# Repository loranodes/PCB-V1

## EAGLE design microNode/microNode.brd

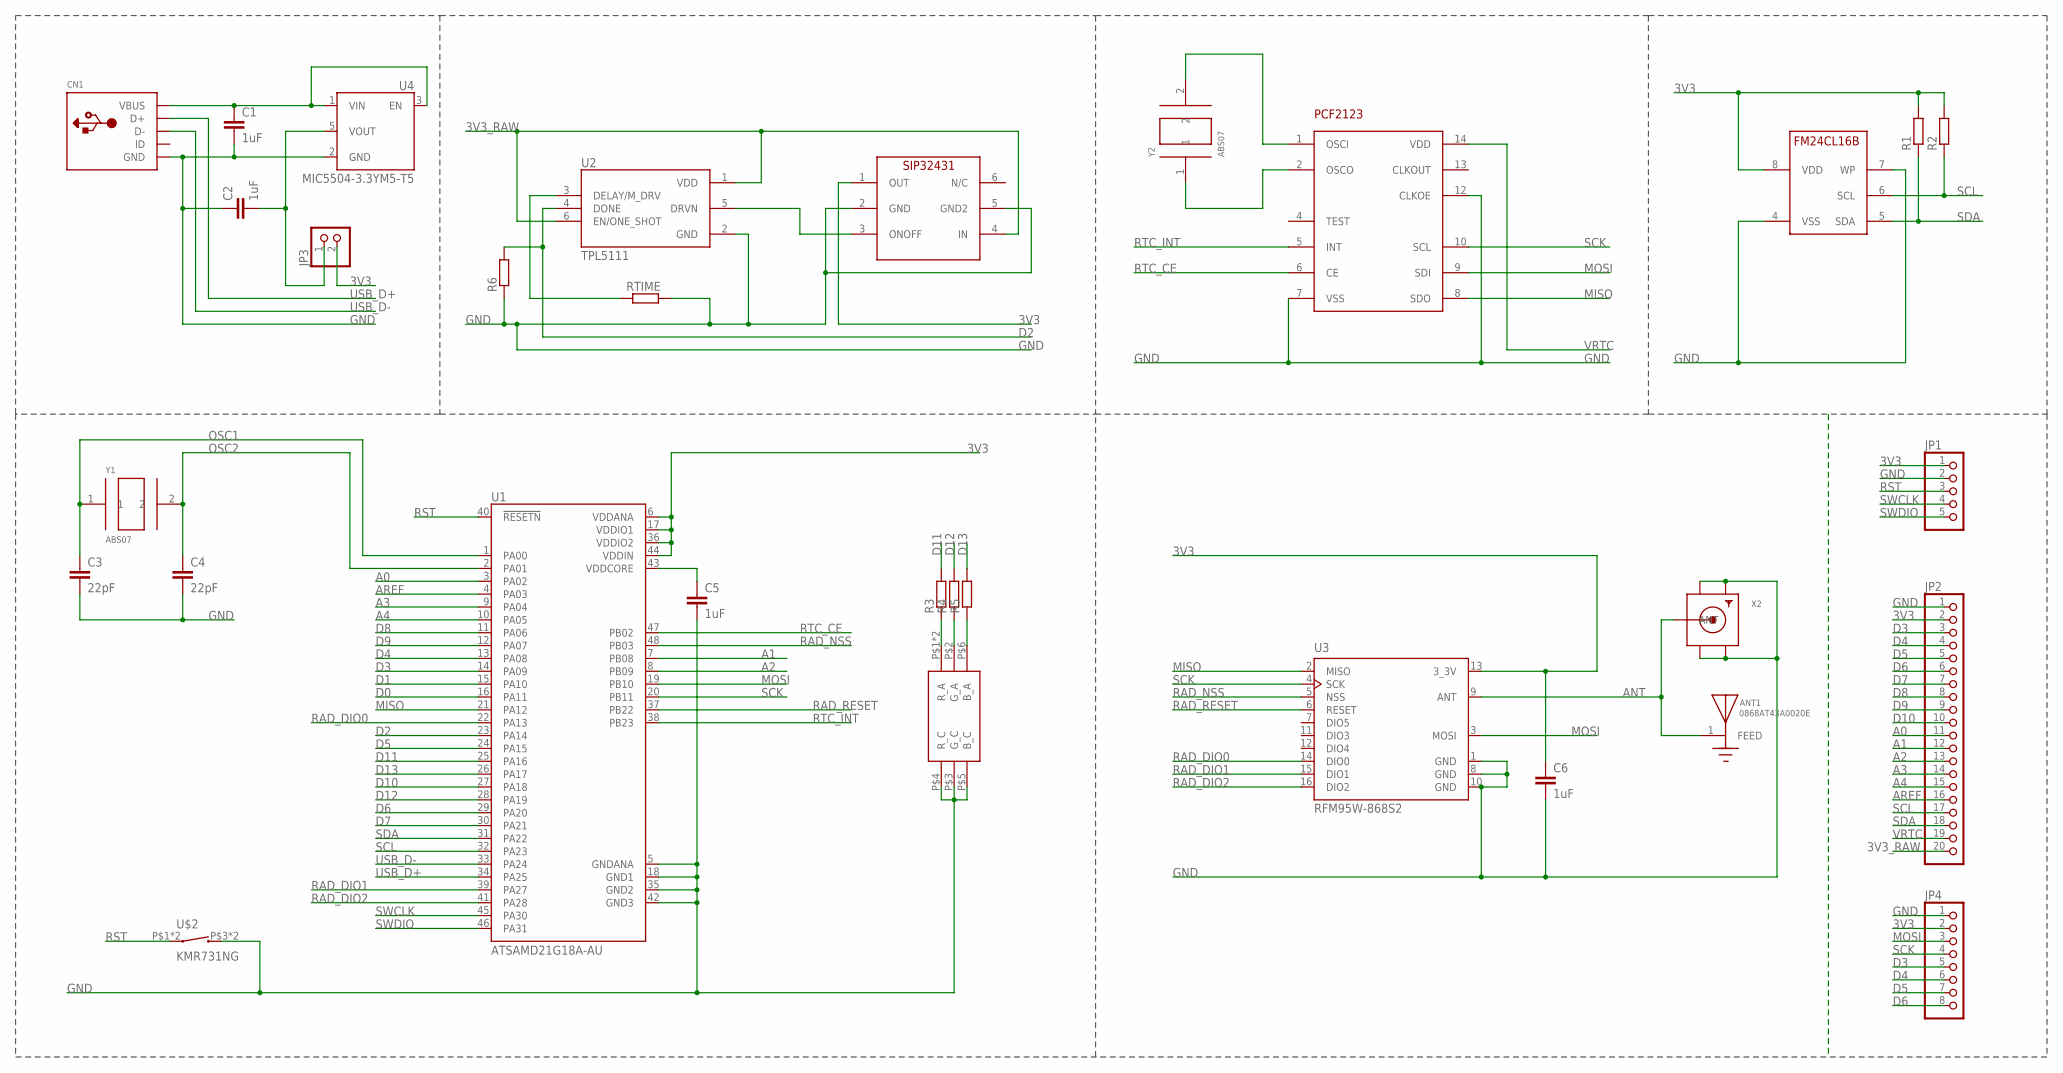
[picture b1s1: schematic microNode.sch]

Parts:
ANT1: 0868AT43A0020E; XCVR_0868AT43A0020E
C1, C2, C5, C6: 1uF; C1206
C3, C4: 22pF; C0603
CN1: USBMINIB; USB-MINIB
JP1: PINHD-1X5; 1X05
JP2: PINHD-1X20; 1X20
JP3: PINHD-1X2; 1X02
JP4: PINHD-1X8; 1X08
R1, R2, R3, R4, R5, R6: RR0603; R0603
RTIME: RR1206; R1206
U1: ATSAMD21G18A-AU; QFP50P900X900X120-48N
U2: TPL5111; SOT95P280X110-6N
U3: RFM95W-868S2; XCVR_RFM95W-868S2
U4: MIC5504-3.3YM5-T5; SOT23-5P95_280X145XL45X37N
U5: FM24CL16B; SOIC-8
U7: SIP32431DR3; SC-70-6
U8: PCF2123; TSSOP14
U$1: MSL0104RGB
U$2: KMR731NG
X2: SMACONNECTOR; SMA90_DIP
Y1, Y2: ABS07; XTAL320X150X90

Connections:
3V3: C6.1, JP1.1, JP2.2, JP3.2, JP4.2, R1.2, R2.2, U1.6 (VDDANA), U1.17 (VDDIO1), U1.36 (VDDIO2), U1.44 (VDDIN), U3.13 (3_3V), U5.8 (VDD), U7.1 (OUT)
3V3_RAW: JP2.20, U2.1 (VDD), U2.6 (EN/ONE_SHOT), U7.4 (IN)
A0: JP2.11, U1.3 (PA02)
A1: JP2.12, U1.7 (PB08)
A2: JP2.13, U1.8 (PB09)
A3: JP2.14, U1.9 (PA04)
A4: JP2.15, U1.10 (PA05)
ANT: ANT1.1, U3.9 (ANT), X2.ANTENNA (ANT)
AREF: JP2.16, U1.4 (PA03)
D0: U1.16 (PA11)
D1: U1.15 (PA10)
D2: R6.2, U1.23 (PA14), U2.4 (DONE)
D3: JP2.3, JP4.5, U1.14 (PA09)
D4: JP2.4, JP4.6, U1.13 (PA08)
D5: JP2.5, JP4.7, U1.24 (PA15)
D6: JP2.6, JP4.8, U1.29 (PA20)
D7: JP2.7, U1.30 (PA21)
D8: JP2.8, U1.11 (PA06)
D9: JP2.9, U1.12 (PA07)
D10: JP2.10, U1.27 (PA18)
D11: R3.2, U1.25 (PA16)
D12: R4.2, U1.28 (PA19)
D13: R5.2, U1.26 (PA17)
GND: C1.2, C2.1, C3.2, C4.2, C5.2, C6.2, CN1.GND, JP1.2, JP2.1, JP4.1, R6.1, RTIME.2, U1.5 (GNDANA), U1.18 (GND1), U1.35 (GND2), U1.42 (GND3), U2.2 (GND), U3.1 (GND), U3.8 (GND), U3.10 (GND), U4.2 (GND), U5.4 (VSS), U5.7 (WP), U7.2 (GND), U7.5 (GND2), U8.7 (VSS), U8.12 (CLKOE), U$1.P$3 (G_C), U$1.P$4 (R_C), U$1.P$5 (B_C), U$2.P$3 (2), U$2.P$4 (2), X2.GND1, X2.GND2, X2.GND3, X2.GND4
MISO: U1.21 (PA12), U3.2 (MISO), U8.8 (SDO)
MOSI: JP4.3, U1.19 (PB10), U3.3 (MOSI), U8.9 (SDI)
unnamed: RTIME.1, U2.3 (DELAY/M_DRV)
unnamed: U2.5 (DRVN), U7.3 (ONOFF)
unnamed: C1.1, CN1.VBUS, U4.1 (VIN), U4.3 (EN)
unnamed: U8.1 (OSCI), Y2.2
unnamed: U8.2 (OSCO), Y2.1
unnamed: C2.2, JP3.1, U4.5 (VOUT)
unnamed: C5.1, U1.43 (VDDCORE)
unnamed: R3.1, U$1.P$1 (R_A), U$1.P$7 (R_A)
unnamed: R4.1, U$1.P$2 (G_A)
unnamed: R5.1, U$1.P$6 (B_A)
OSC1: C3.1, U1.1 (PA00), Y1.1
OSC2: C4.1, U1.2 (PA01), Y1.2
RAD_DIO0: U1.22 (PA13), U3.14 (DIO0)
RAD_DIO1: U1.39 (PA27), U3.15 (DIO1)
RAD_DIO2: U1.41 (PA28), U3.16 (DIO2)
RAD_NSS: U1.48 (PB03), U3.5 (NSS)
RAD_RESET: U1.37 (PB22), U3.6 (RESET)
RST: JP1.3, U1.40 (!RESETN), U$2.P$1 (1), U$2.P$2 (1)
RTC_CE: U1.47 (PB02), U8.6 (CE)
RTC_INT: U1.38 (PB23), U8.5 (INT)
SCK: JP4.4, U1.20 (PB11), U3.4 (SCK), U8.10 (SCL)
SCL: JP2.17, R2.1, U1.32 (PA23), U5.6 (SCL)
SDA: JP2.18, R1.1, U1.31 (PA22), U5.5 (SDA)
SWCLK: JP1.4, U1.45 (PA30)
SWDIO: JP1.5, U1.46 (PA31)
USB_D+: CN1.D+, U1.34 (PA25)
USB_D-: CN1.D-, U1.33 (PA24)
VRTC: JP2.19, U8.14 (VDD)

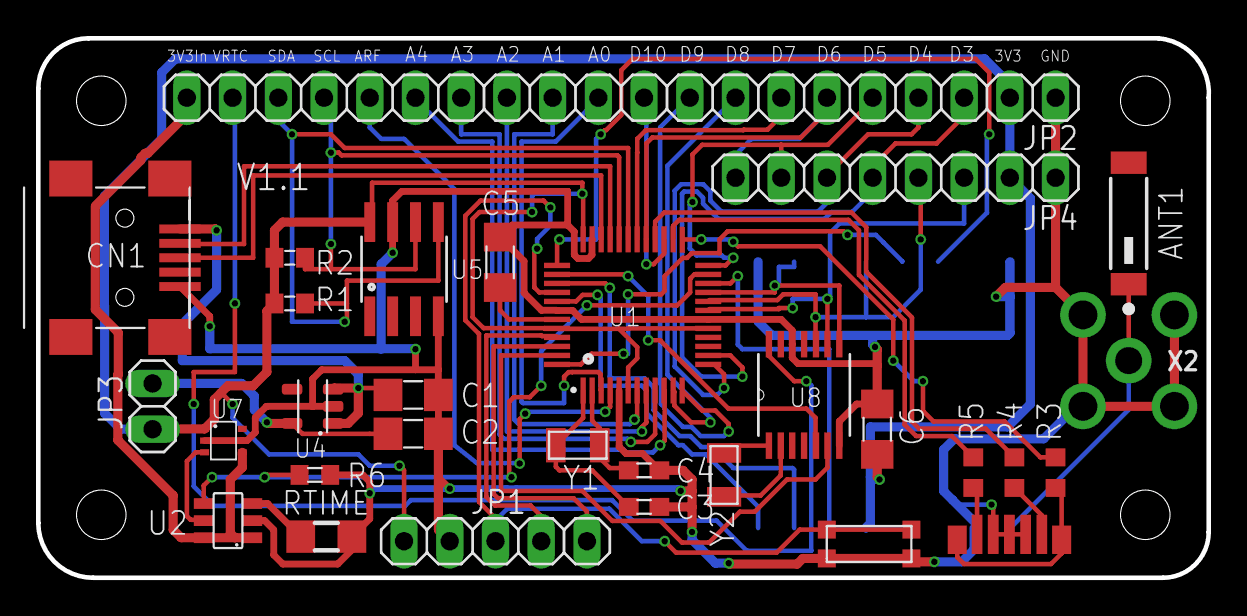
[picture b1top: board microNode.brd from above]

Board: 2 copper layers, 65.0 x 30.0 mm, 31 parts (1 on the bottom side), 52 nets.

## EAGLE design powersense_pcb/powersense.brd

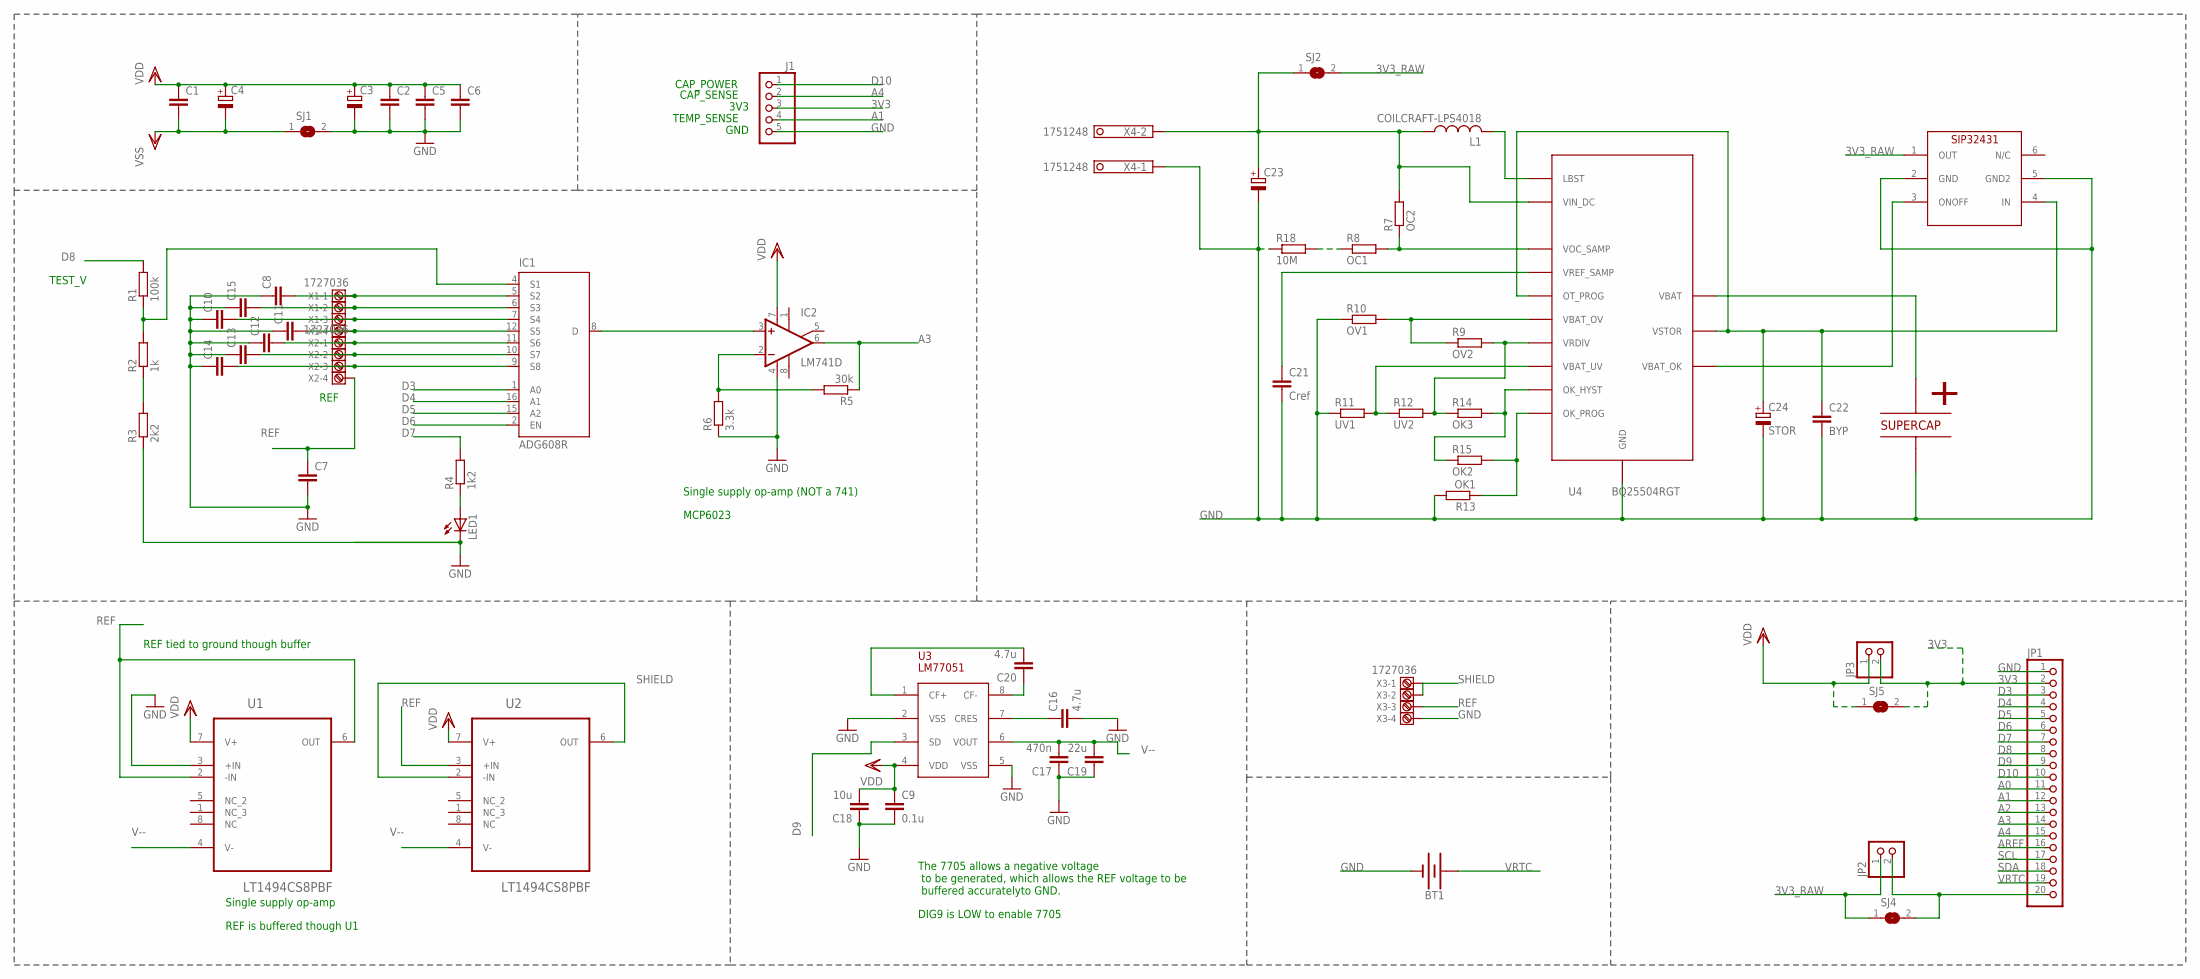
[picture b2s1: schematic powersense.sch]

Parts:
BT1: BATTERY-20MM_SMD; BATTCON_20MM
C1, C2, C5, C6, C7, C8, C10, C11, C12, C13, C14, C15: C-EUC1206; C1206
C3, C4, C23: CPOL-EUE5-6; E5-6
C9: 0.1u; C1206
C16, C20: 4.7u; C1206
C17: 470n; C1206
C18: 10u; C1206
C19: 22u; C1206
C21: Cref; C1206
C22: BYP; C1206
C24: STOR; E5-6
IC1: ADG608R; SOIC16N
IC2: LM741D; SO08
J1: PINHD-1X5; 1X05
JP1: PINHD-1X20; 1X20
JP2, JP3: PINHD-1X2; 1X02
L1: COILCRAFT-LPS4018; LPS4018
LED1: LEDCHIPLED_0805; CHIPLED_0805
R1: 100k; R1206
R2: 1k; R1206
R3: 2k2; R1206
R4: 1k2; R1206
R5: 30k; R1206
R6: 3.3k; R1206
R7: OC2; R0603
R8: OC1; R0603
R9: OV2; R0603
R10: OV1; R0603
R11: UV1; R0603
R12: UV2; R0603
R13: OK1; R0603
R14: OK3; R0603
R15: OK2; R0603
R18: 10M; R0603
SJ1, SJ2, SJ4, SJ5: SJ
U1, U2: LT1494CS8PBF; SOIC127P600X175-8N
U3: LM77051; S-PDSO-G08_N
U4: BQ25504RGT; S-PVQFN-N16
U5: SIP32431DR3; SC-70-6
U$2: DDL105S05F1JRRDAPZ; CAPF1J
X1, X2, X3: 1727036
X4: 1751248

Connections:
3V3: J1.3, JP1.2, JP3.2, SJ5.2
3V3_RAW: JP2.1, SJ2.2, SJ4.1, U5.1 (OUT)
A0: JP1.11
A1: J1.4, JP1.12
A2: JP1.13
A3: IC2.6 (OUT), JP1.14, R5.1
A4: J1.2, JP1.15
AREF: JP1.16
D3: IC1.1 (A0), JP1.3
D4: IC1.16 (A1), JP1.4
D5: IC1.15 (A2), JP1.5
D6: IC1.2 (EN), JP1.6
D7: JP1.7, R4.2
D8: JP1.8, R1.2
D9: JP1.9, U3.3 (SD)
D10: J1.1, JP1.10
GND: BT1.2 (-), C2.2, C3.-, C5.2, C6.2, C7.2, C8.1, C9.2, C10.1, C11.1, C12.1, C13.1, C14.1, C15.1, C16.2, C17.1, C18.1, C19.1, C21.2, C22.2, C23.-, C24.-, IC1.14 (GND), IC2.4 (V-), J1.5, JP1.1, LED1.C, R3.1, R6.1, R10.1, R11.1, R13.2, R18.1, SJ1.2, U1.3 (+IN), U3.2 (VSS), U3.5 (VSS), U4.1 (GND), U4.12 (GND), U4.13 (GND), U5.2 (GND), U5.5 (GND2), U$2.P$2, X3.4, X4.1
JEFF: U4.14 (VBAT), U$2.P$1
unnamed: IC1.4 (S1), R1.1, R2.2
unnamed: C8.2, IC1.5 (S2), X1.1
unnamed: IC2.2 (-IN), R5.2, R6.2
unnamed: IC1.8 (D), IC2.3 (+IN)
unnamed: R7.1, R8.2, U4.3 (VOC_SAMP)
unnamed: C20.2, U3.1 (CF+)
unnamed: C20.1, U3.8 (CF-)
unnamed: C16.1, U3.7 (CRES)
unnamed: U4.11 (VBAT_OK), U5.3 (ONOFF)
unnamed: LED1.A, R4.1
unnamed: C21.1, U4.4 (VREF_SAMP)
unnamed: R2.1, R3.2
unnamed: C22.1, C24.+, U4.5 (OT_PROG), U4.15 (VSTOR), U5.4 (IN)
unnamed: R9.1, R10.2, U4.6 (VBAT_OV)
unnamed: R14.2, R15.1, U4.9 (OK_HYST)
unnamed: R9.2, R12.2, R14.1, U4.7 (VRDIV)
unnamed: R11.2, R12.1, U4.8 (VBAT_UV)
unnamed: R13.1, R15.2, U4.10 (OK_PROG)
unnamed: L1.2, U4.16 (LBST)
unnamed: JP1.20, JP2.2, SJ4.2
unnamed: C15.2, IC1.6 (S3), X1.2
unnamed: C10.2, IC1.7 (S4), X1.3
unnamed: C11.2, IC1.12 (S5), X1.4
unnamed: C12.2, IC1.11 (S6), X2.1
unnamed: C13.2, IC1.10 (S7), X2.2
unnamed: C14.2, IC1.9 (S8), X2.3
unnamed: R8.1, R18.2
PIN: C23.+, L1.1, R7.2, SJ2.1, U4.2 (VIN_DC), X4.2
REF: C7.1, U1.2 (-IN), U1.6 (OUT), U2.3 (+IN), X2.4, X3.3
SCL: JP1.17
SDA: JP1.18
SHIELD: U2.2 (-IN), U2.6 (OUT), X3.1, X3.2
V--: C17.2, C19.2, U1.4 (V-), U2.4 (V-), U3.6 (VOUT)
VDD: C1.1, C2.1, C3.+, C4.+, C5.1, C6.1, C9.1, C18.2, IC1.13 (VDD), IC2.7 (V+), JP3.1, SJ5.1, U1.7 (V+), U2.7 (V+), U3.4 (VDD)
VRTC: BT1.1 (+), JP1.19
VSS: C1.2, C4.-, IC1.3 (VSS), SJ1.1

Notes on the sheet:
REF
REF is buffered though U1
REF tied to ground though buffer
Single supply op-amp
TEST_V
Single supply op-amp (NOT a 741)
MCP6023
DIG9 is LOW to enable 7705
The 7705 allows a negative voltage to be generated, which allows the REF voltage to be buffered accuratelyto GND.
CAP_POWER
CAP_SENSE
3V3
TEMP_SENSE
GND

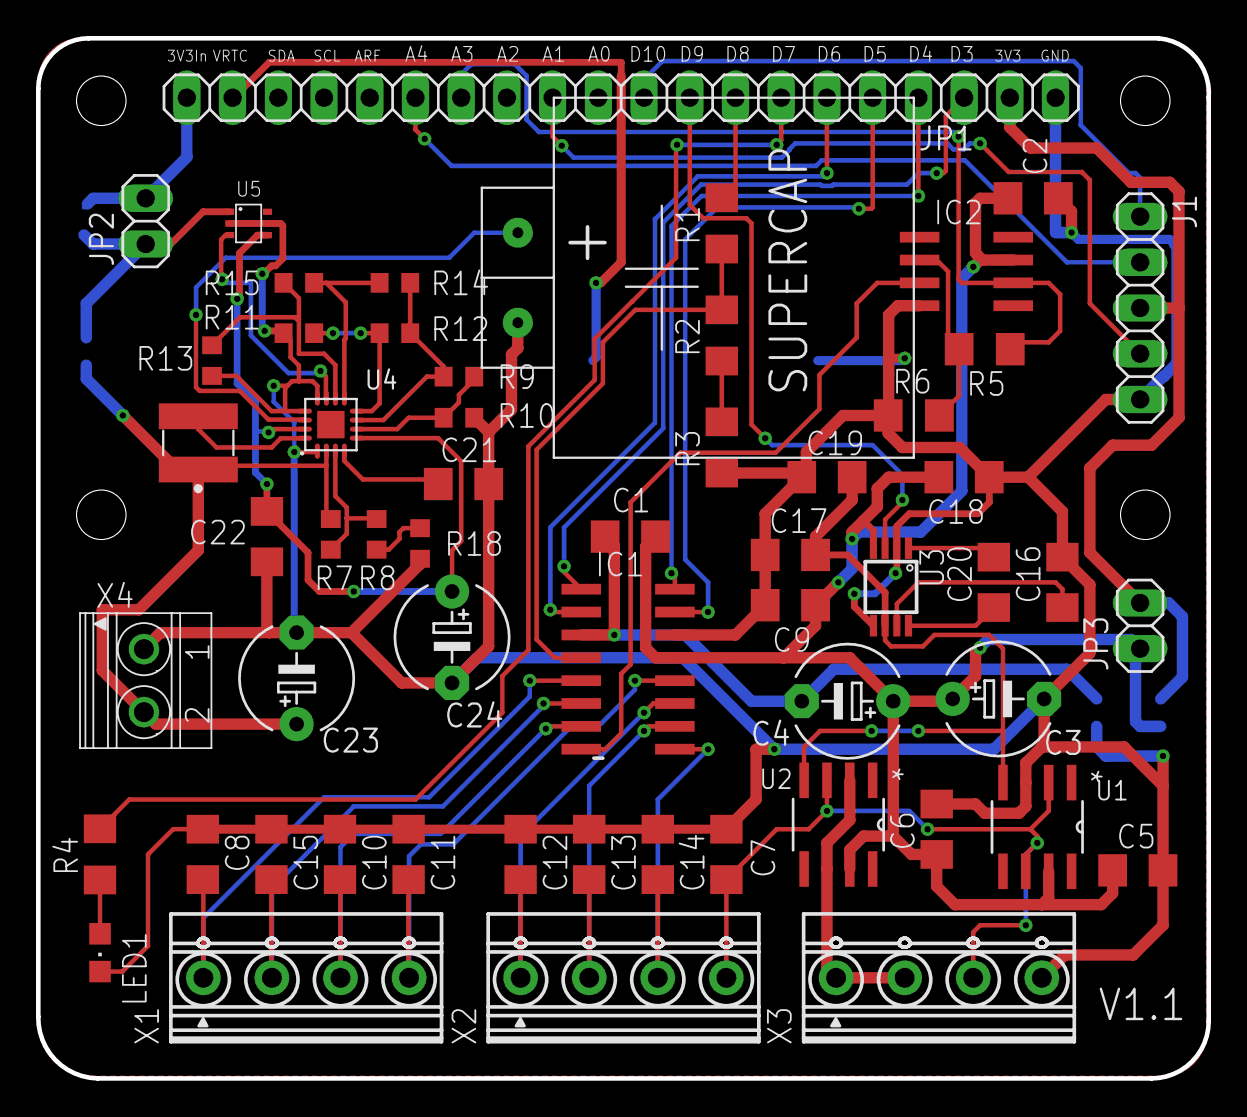
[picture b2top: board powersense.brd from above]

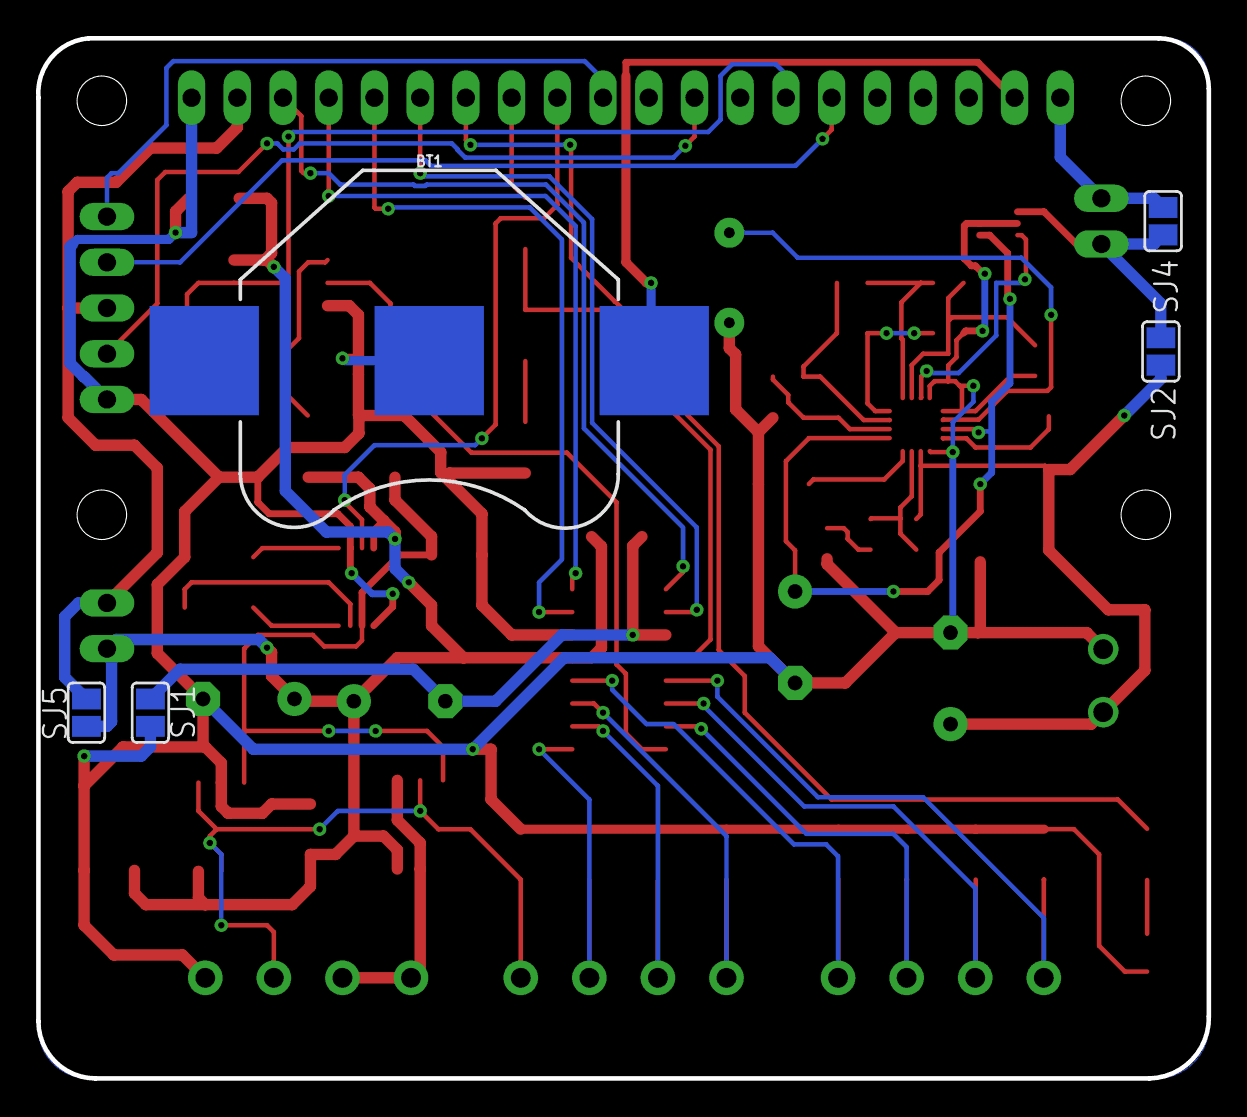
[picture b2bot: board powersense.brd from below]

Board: 2 copper layers, 65.0 x 57.8 mm, 63 parts (5 on the bottom side), 49 nets.

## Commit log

2018-07-25 Added all the PCB stuff from previous repo
2018-08-14 Display connector/ RST button/ side led
2018-08-14 Finished V1.0 of display adaptor
2018-08-14 changed coin cell holder
2018-08-14 Added version number to micronode
2018-08-14 Added notch to display adaptor to fit over SMA

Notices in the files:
parts and their libraries:
SparkFun-Batteries: Licensing: Creative Commons ShareAlike 4.0 International - https://creativecommons.org/licenses/by-sa/4.0
